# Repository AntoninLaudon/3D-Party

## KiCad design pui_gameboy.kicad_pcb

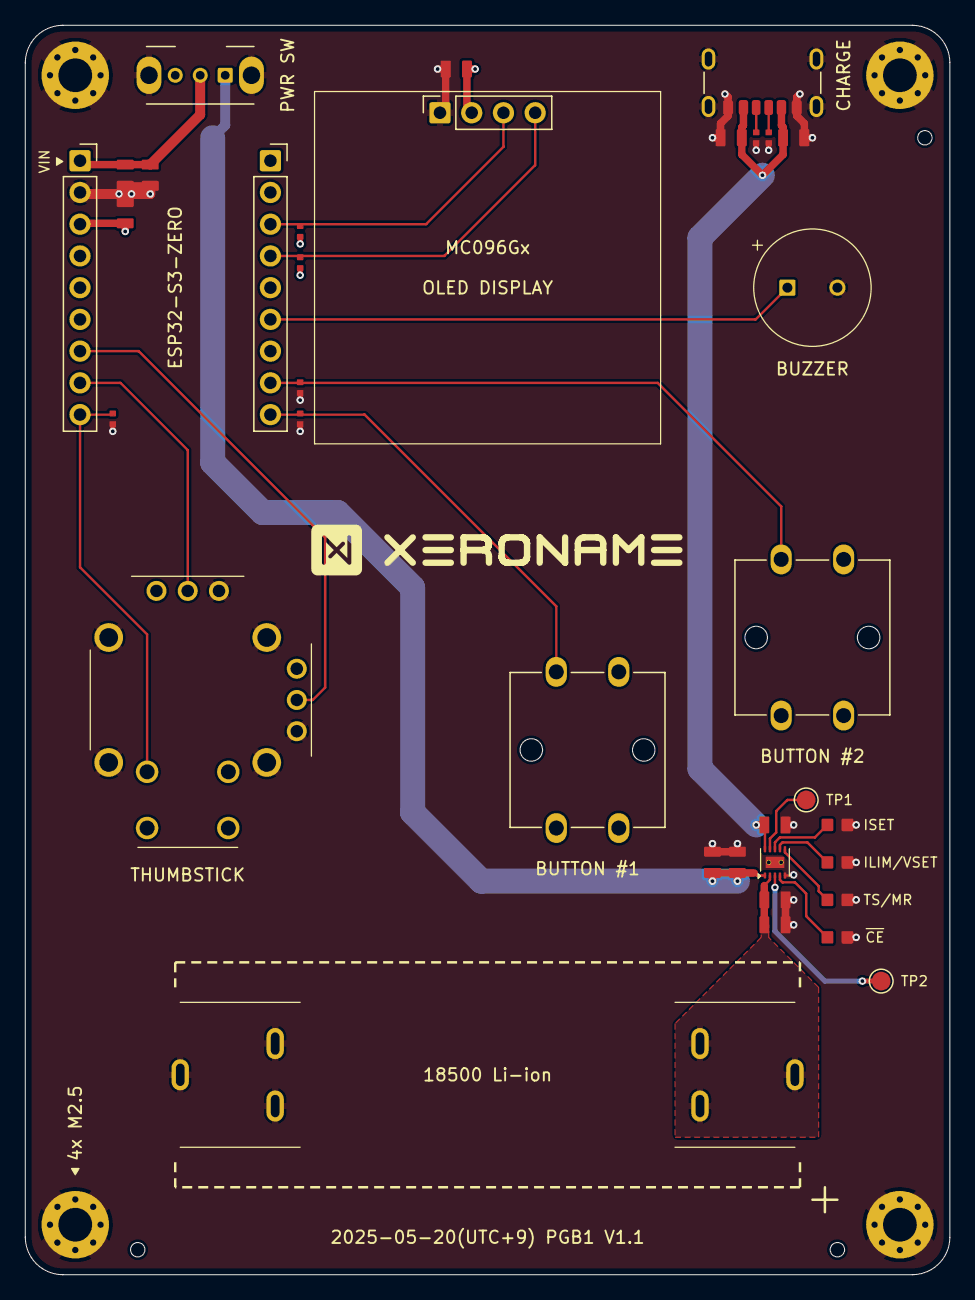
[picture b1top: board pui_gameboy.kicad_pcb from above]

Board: 4 copper layers, 74.0 x 100.0 mm, 43 parts (0 on the bottom side), 22 nets.

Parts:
C1, C2, C3, C4, C5, C6, C7, C8, C9, C10, C11: 0805_2013Metric_IPC_Least
J1, J2: PinSocket_1x09_P2.54mm_Vertical
J3: PinSocket_1x04_P2.54mm_Vertical
J4: USB_C_Receptacle_GCT_USB4125-xx-x_6P_TopMnt_Horiz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; USB_C_Receptacle_GCT_USB4125-xx-x_6P_TopMnt_Horizontal
J5, J6: MYOUNG_Battery_Contact_MY-18650-01
LS1: Buzzer_Radial_P4.0mm_D9.0mm_H5.5mm
MH: MountingHole_2.7mm_M2.5_Pad_Via
MH#2, MH#3, MH#4: MountingHole_2.7mm_M2.5_Pad_Via
R1, R2, R7, R8, R9, R10, R11: 0402_1005Metric_IPC_Least
R3, R4, R5, R6: 0603_1608Metric_IPC_Nominal
S1: C&K_THB001P_joystick_thumbstick
S2, S3: SW_SPST_Omron_B3F-40xx
S4: SW_Slide_SPDT_Angled_CK_OS102011MA1Q
TH: ToolingHole_1.152mm
TH#2, TH#3: ToolingHole_1.152mm
TP1, TP2: TestPoint_Pad_D1.5mm
U1: TI_DLH_WSON-10-EP1_2.0x2.2mm_P0.4mm_EP0.9x1.5mm_T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; TI_DLH_WSON-10-EP1_2.0x2.2mm_P0.4mm_EP0.9x1.5mm_ThermalVias

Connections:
B1.OUT: J2.9, R8.2, S2.1
B2.OUT: J2.8, R9.2, S3.1
BC.CE: R3.1, U1.4
BC.ISET: R6.1, U1.8
BC.STAT1: TP1.1, U1.9
BC.STAT2: TP2.1, U1.3
BC.TSMR: R4.1, U1.6
BC.VSET: R5.1, U1.7
BUZ.IN: J2.6, LS1.1
DISP.SCL: J2.3, J3.3, R11.2
DISP.SDA: J2.4, J3.4, R10.2
ESP.VIN: C1.2, C2.2, J1.1, S4.2
GND: C1.1, C2.1, C3.2, C4.1, C5.1, C6.2, C7.2, C8.2, C9.2, C10.2, C11.2, J1.2, J3.1, J4.A12, J4.B12, J4.S1, J5.MP, LS1.2, MH.1, MH#2.1, MH#3.1, MH#4.1, R1.1, R2.1, R3.2, R4.2, R5.2, R6.2, R7.1, R8.1, R9.1, S1.1, S1.1', S1.MP, U1.5, U1.11
PWR.3V3: C3.1, C4.2, J1.3, J3.2, R10.1, R11.1, S1.3, S1.3', S1.C, S2.2, S3.2
PWR.VBAT: C9.1, C10.1, J6.MP, U1.2
PWR.VBUS: C5.2, C6.1, C11.1, J4.A9, J4.B9, U1.10
PWR.VSYS: C7.1, C8.1, S4.1, U1.1
TMB.BOUT: J1.9, R7.2, S1.A
TMB.OUTX: J1.8, S1.2
TMB.OUTY: J1.7, S1.2'
USB.CC1: J4.A5, R1.2
USB.CC2: J4.B5, R2.2

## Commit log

2025-05-12 feat(games): Interface for game and example game
2025-05-13 feat(menu): Add basic menu for game selection
2025-05-21 feat(games): Refactor game format, add new games
2025-05-21 other way of counting games
2025-05-22 Refactor functional code to oop
2025-05-22 Fix warnings
2025-05-22 Refactor network to be in namespace
2025-05-24 Add KiCad PCB work files
    Edited in KiCad 9.0.1
2025-05-24 Rename pui_gameboy.kicad_prl to PCB/pui_gameboy.kicad_prl
2025-05-24 Rename pui_gameboy.kicad_pro to PCB/pui_gameboy.kicad_pro
2025-05-24 Rename pui_gameboy.kicad_sch to PCB/pui_gameboy.kicad_sch
2025-05-26 Add compiling network
2025-05-28 feat(games): Add Minesweeper and Memory, refactor Menu
2025-06-10 feat(networking): GAMES
